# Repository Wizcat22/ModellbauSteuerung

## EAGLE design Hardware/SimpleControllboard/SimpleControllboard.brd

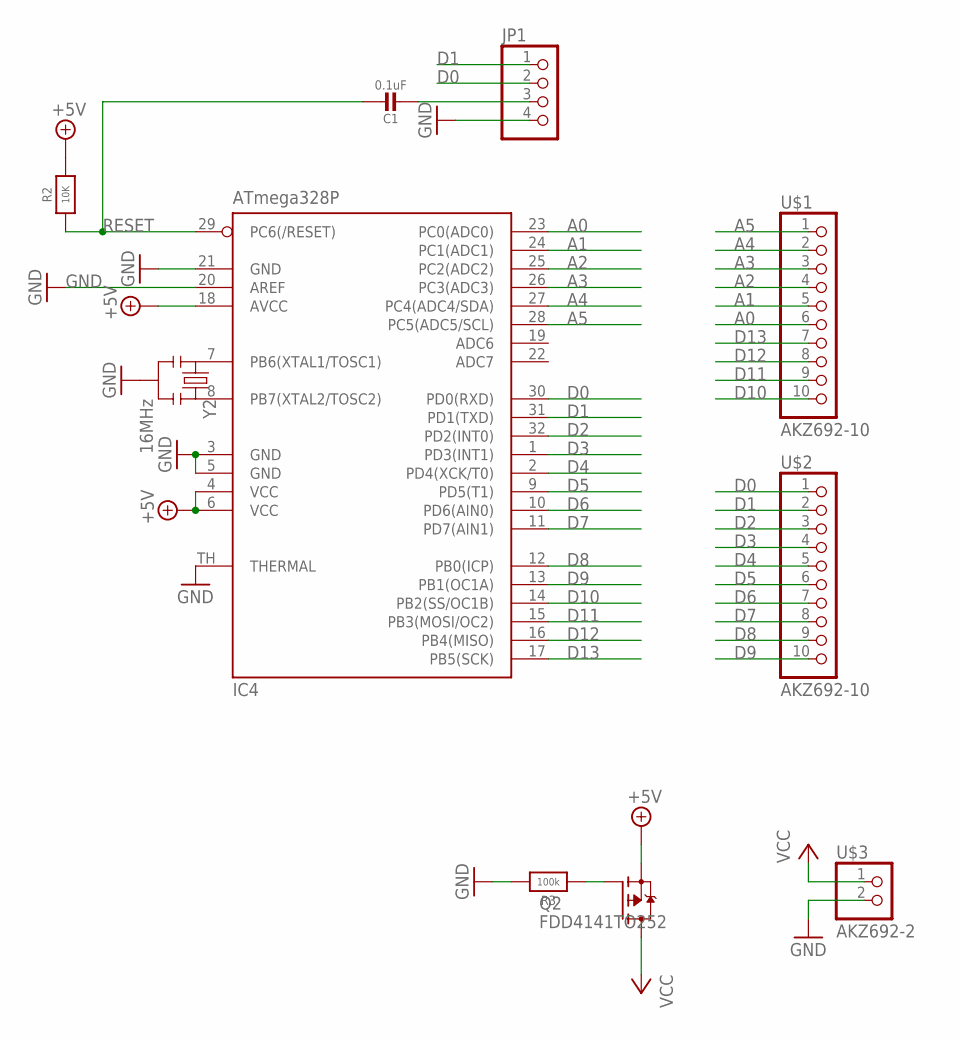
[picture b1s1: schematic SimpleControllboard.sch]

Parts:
C1: 0.1uF; 0805-NO
IC4: ATmega328P; MLF32-TH
JP1: PINHD-1X4; 1X04
Q2: FDD4141TO252; TO252
R2: 10K; 0805-NO
R3: 100k; 0805-NO
U$1, U$2: AKZ692-10; 1X10
U$3: AKZ692-2; 1X2
Y2: 16MHz; RESONATOR-SMD

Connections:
+5V: IC4.4 (VCC), IC4.6 (VCC), IC4.18 (AVCC), Q2.2 (S), R2.2
A0: IC4.23 (PC0(ADC0)), U$1.6
A1: IC4.24 (PC1(ADC1)), U$1.5
A2: IC4.25 (PC2(ADC2)), U$1.4
A3: IC4.26 (PC3(ADC3)), U$1.3
A4: IC4.27 (PC4(ADC4/SDA)), U$1.2
A5: IC4.28 (PC5(ADC5/SCL)), U$1.1
D0: IC4.30 (PD0(RXD)), JP1.2, U$2.1
D1: IC4.31 (PD1(TXD)), JP1.1, U$2.2
D2: IC4.32 (PD2(INT0)), U$2.3
D3: IC4.1 (PD3(INT1)), U$2.4
D4: IC4.2 (PD4(XCK/T0)), U$2.5
D5: IC4.9 (PD5(T1)), U$2.6
D6: IC4.10 (PD6(AIN0)), U$2.7
D7: IC4.11 (PD7(AIN1)), U$2.8
D8: IC4.12 (PB0(ICP)), U$2.9
D9: IC4.13 (PB1(OC1A)), U$2.10
D10: IC4.14 (PB2(SS/OC1B)), U$1.10
D11: IC4.15 (PB3(MOSI/OC2)), U$1.9
D12: IC4.16 (PB4(MISO)), U$1.8
D13: IC4.17 (PB5(SCK)), U$1.7
DTR/RTS1: C1.2, JP1.3
GND: IC4.3 (GND), IC4.5 (GND), IC4.20 (AREF), IC4.21 (GND), IC4.TH (THERMAL), JP1.4, R3.2, U$3.2, Y2.2
unnamed: IC4.8 (PB7(XTAL2/TOSC2)), Y2.3
unnamed: IC4.7 (PB6(XTAL1/TOSC1)), Y2.1
unnamed: Q2.1 (G), R3.1
RESET: C1.1, IC4.29 (PC6(/RESET)), R2.1
VCC: Q2.3 (D), U$3.1

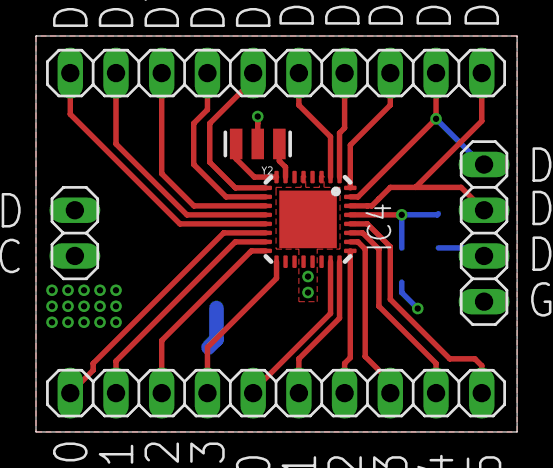
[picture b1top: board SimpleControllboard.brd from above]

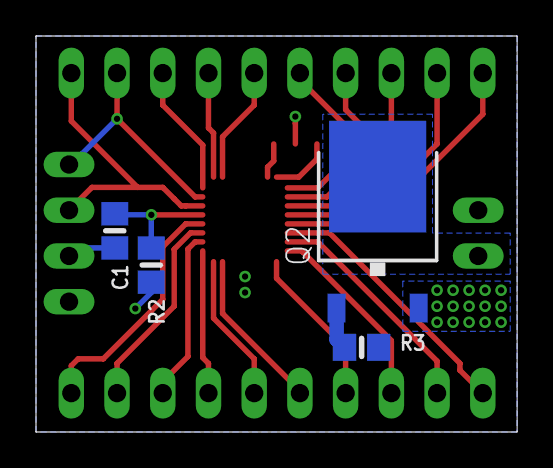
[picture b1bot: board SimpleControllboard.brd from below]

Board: 2 copper layers, 26.7 x 22.0 mm, 10 parts (4 on the bottom side), 28 nets.

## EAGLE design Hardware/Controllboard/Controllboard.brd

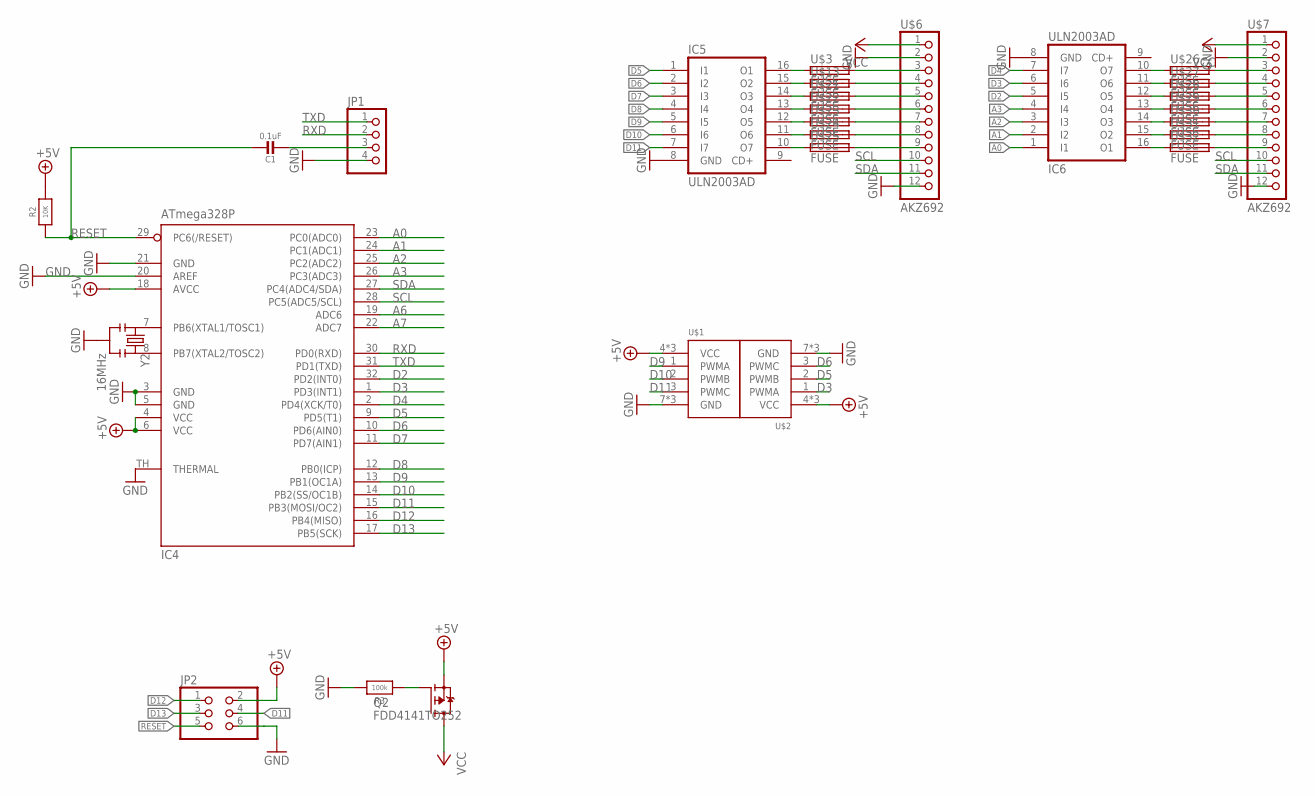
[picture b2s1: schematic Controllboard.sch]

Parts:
C1: 0.1uF; 0805-NO
IC4: ATmega328P; MLF32-TH
IC5, IC6: ULN2003AD; SO16
JP1: PINHD-1X4; 1X04
JP2: PINHD-2X3M; 2X03M
Q2: FDD4141TO252; TO252
R2: 10K; 0805-NO
R3: 100k; 0805-NO
U$1, U$2: SERVO_X3; 2X03/90
U$3, U$13, U$21, U$22, U$23, U$24, U$25, U$26, U$27, U$28, U$29, U$30, U$31, U$32: FUSE; C1206
U$6, U$7: AKZ692; 1X12
Y2: 16MHz; RESONATOR-SMD

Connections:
+5V: IC4.4 (VCC), IC4.6 (VCC), IC4.18 (AVCC), JP2.2, Q2.2 (S), R2.2, U$1.4 (VCC), U$1.5 (VCC), U$1.6 (VCC), U$2.4 (VCC), U$2.5 (VCC), U$2.6 (VCC)
A0: IC4.23 (PC0(ADC0)), IC6.1 (I1)
A1: IC4.24 (PC1(ADC1)), IC6.2 (I2)
A2: IC4.25 (PC2(ADC2)), IC6.3 (I3)
A3: IC4.26 (PC3(ADC3)), IC6.4 (I4)
A6: IC4.19 (ADC6)
A7: IC4.22 (ADC7)
D2: IC4.32 (PD2(INT0)), IC6.5 (I5)
D3: IC4.1 (PD3(INT1)), IC6.6 (I6), U$2.1 (PWMA)
D4: IC4.2 (PD4(XCK/T0)), IC6.7 (I7)
D5: IC4.9 (PD5(T1)), IC5.1 (I1), U$2.2 (PWMB)
D6: IC4.10 (PD6(AIN0)), IC5.2 (I2), U$2.3 (PWMC)
D7: IC4.11 (PD7(AIN1)), IC5.3 (I3)
D8: IC4.12 (PB0(ICP)), IC5.4 (I4)
D9: IC4.13 (PB1(OC1A)), IC5.5 (I5), U$1.1 (PWMA)
D10: IC4.14 (PB2(SS/OC1B)), IC5.6 (I6), U$1.2 (PWMB)
D11: IC4.15 (PB3(MOSI/OC2)), IC5.7 (I7), JP2.4, U$1.3 (PWMC)
D12: IC4.16 (PB4(MISO)), JP2.1
D13: IC4.17 (PB5(SCK)), JP2.3
DTR/RTS1: C1.2, JP1.3
GND: IC4.3 (GND), IC4.5 (GND), IC4.20 (AREF), IC4.21 (GND), IC4.TH (THERMAL), IC5.8 (GND), IC6.8 (GND), JP1.4, JP2.6, R3.2, U$1.7 (GND), U$1.8 (GND), U$1.9 (GND), U$2.7 (GND), U$2.8 (GND), U$2.9 (GND), U$6.2, U$6.12, U$7.2, U$7.12, Y2.2
unnamed: IC4.8 (PB7(XTAL2/TOSC2)), Y2.3
unnamed: IC4.7 (PB6(XTAL1/TOSC1)), Y2.1
unnamed: U$3.2, U$6.3
unnamed: U$6.4, U$13.2
unnamed: U$6.5, U$21.2
unnamed: U$6.6, U$22.2
unnamed: U$6.7, U$23.2
unnamed: U$6.8, U$24.2
unnamed: U$6.9, U$25.2
unnamed: U$7.3, U$26.2
unnamed: U$7.4, U$27.2
unnamed: U$7.5, U$28.2
unnamed: U$7.6, U$29.2
unnamed: U$7.7, U$30.2
unnamed: U$7.8, U$31.2
unnamed: U$7.9, U$32.2
unnamed: IC5.16 (O1), U$3.1
unnamed: IC5.15 (O2), U$13.1
unnamed: IC5.14 (O3), U$21.1
unnamed: IC5.13 (O4), U$22.1
unnamed: IC5.12 (O5), U$23.1
unnamed: IC5.11 (O6), U$24.1
unnamed: IC5.10 (O7), U$25.1
unnamed: IC6.10 (O7), U$26.1
unnamed: IC6.11 (O6), U$27.1
unnamed: IC6.12 (O5), U$28.1
unnamed: IC6.13 (O4), U$29.1
unnamed: IC6.14 (O3), U$30.1
unnamed: IC6.15 (O2), U$31.1
unnamed: IC6.16 (O1), U$32.1
unnamed: Q2.1 (G), R3.1
RESET: C1.1, IC4.29 (PC6(/RESET)), JP2.5, R2.1
RXD: IC4.30 (PD0(RXD)), JP1.2
SCL: IC4.28 (PC5(ADC5/SCL)), U$6.10, U$7.10
SDA: IC4.27 (PC4(ADC4/SDA)), U$6.11, U$7.11
TXD: IC4.31 (PD1(TXD)), JP1.1
VCC: Q2.3 (D), U$6.1, U$7.1

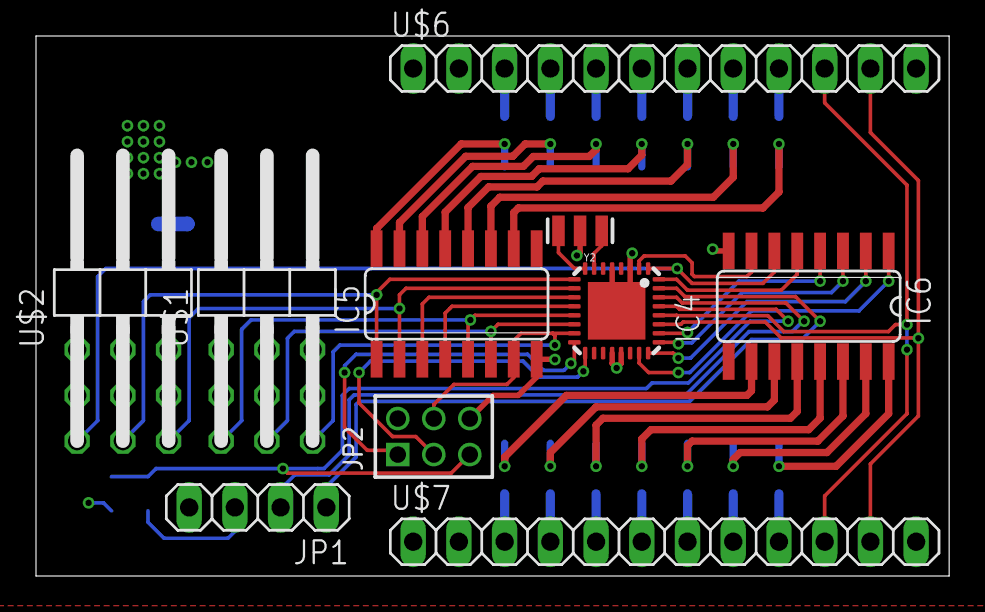
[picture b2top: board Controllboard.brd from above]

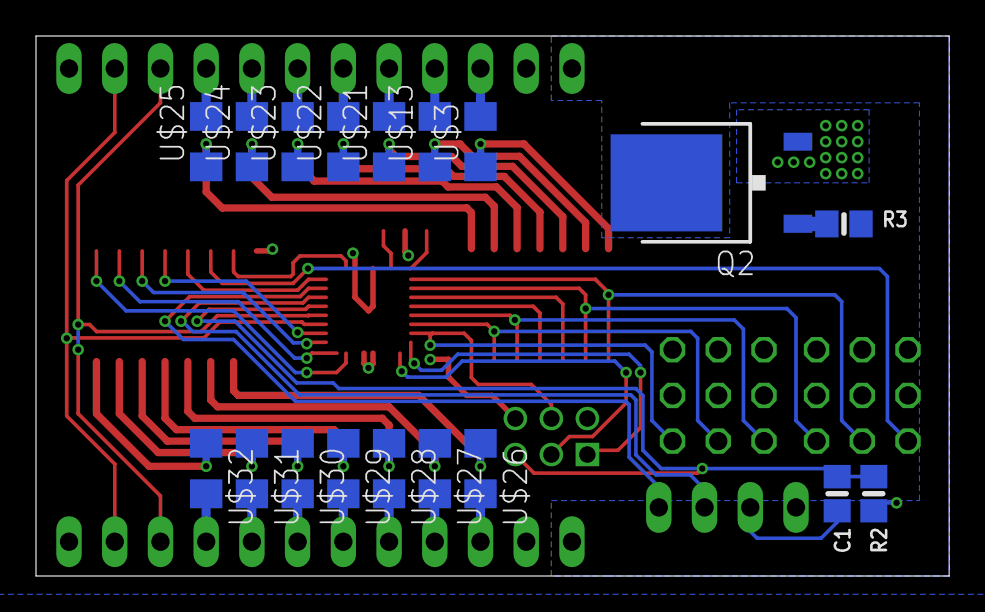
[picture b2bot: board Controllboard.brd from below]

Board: 2 copper layers, 50.7 x 30.0 mm, 28 parts (18 on the bottom side), 56 nets.

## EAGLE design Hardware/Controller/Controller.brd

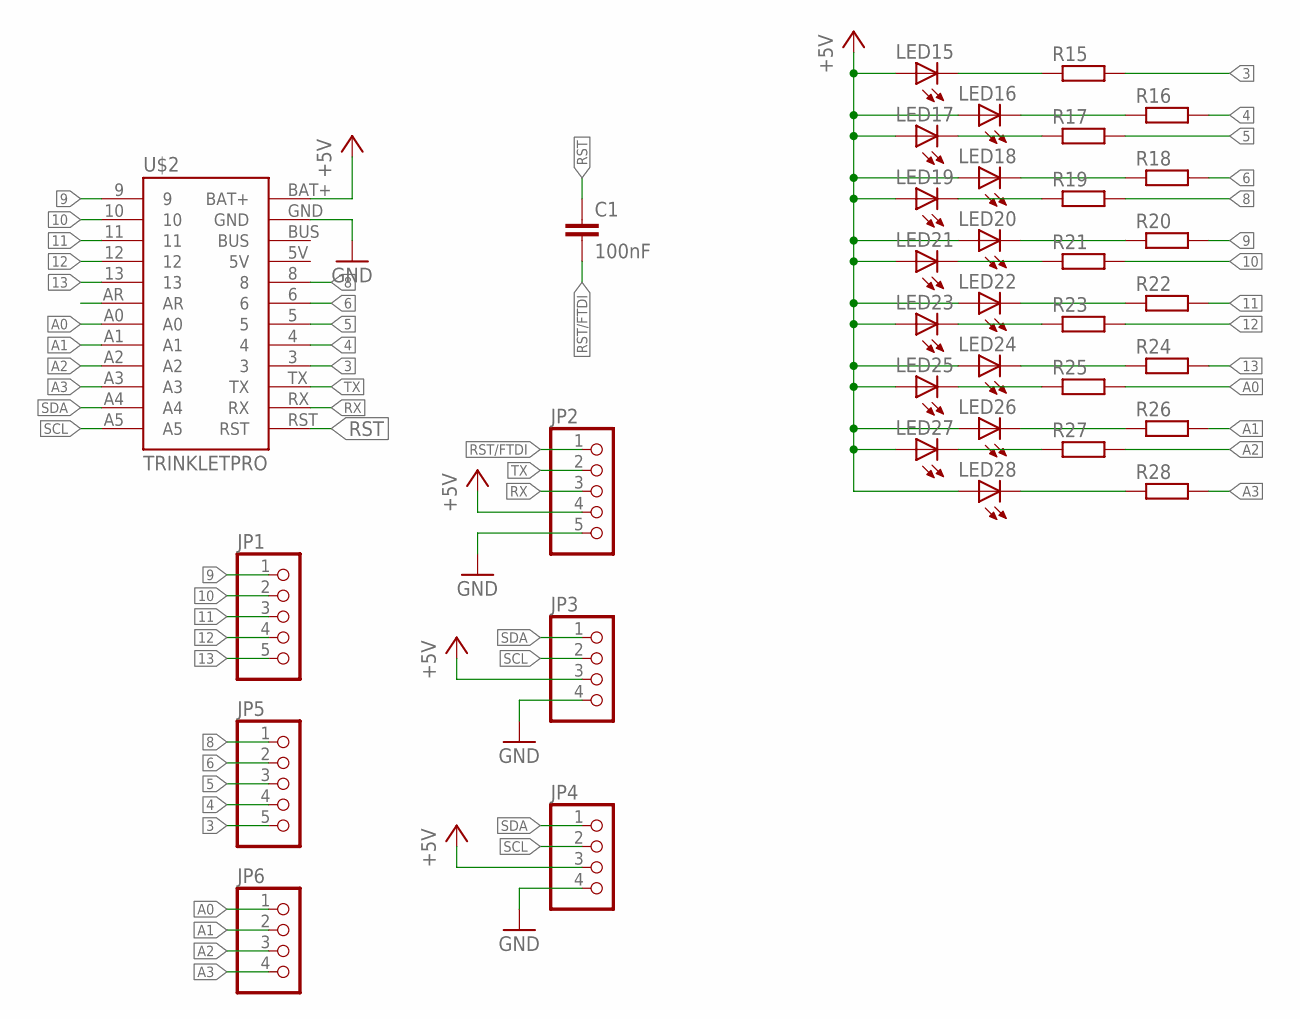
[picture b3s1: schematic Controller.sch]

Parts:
C1: 100nF; C0805
JP1, JP2, JP5: PINHD-1X5; 1X05
JP3, JP4, JP6: PINHD-1X4; 1X04
LED15, LED16, LED17, LED18, LED19, LED20, LED21, LED22, LED23, LED24, LED25, LED26, LED27, LED28: LEDCHIP-LED0805; CHIP-LED0805
R15, R16, R17, R18, R19, R20, R21, R22, R23, R24, R25, R26, R27, R28: R-EU_R0805; R0805
U$2: TRINKLETPRO; 1X12

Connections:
3: JP5.5, R15.2, U$2.3
4: JP5.4, R16.2, U$2.4
5: JP5.3, R17.2, U$2.5
6: JP5.2, R18.2, U$2.6
8: JP5.1, R19.2, U$2.8
9: JP1.1, R20.2, U$2.9
10: JP1.2, R21.2, U$2.10
11: JP1.3, R22.2, U$2.11
12: JP1.4, R23.2, U$2.12
13: JP1.5, R24.2, U$2.13
+5V: JP2.4, JP3.3, JP4.3, LED15.A, LED16.A, LED17.A, LED18.A, LED19.A, LED20.A, LED21.A, LED22.A, LED23.A, LED24.A, LED25.A, LED26.A, LED27.A, LED28.A, U$2.BAT+
A0: JP6.1, R25.2, U$2.A0
A1: JP6.2, R26.2, U$2.A1
A2: JP6.3, R27.2, U$2.A2
A3: JP6.4, R28.2, U$2.A3
GND: JP2.5, JP3.4, JP4.4, U$2.GND
unnamed: LED15.C, R15.1
unnamed: LED16.C, R16.1
unnamed: LED17.C, R17.1
unnamed: LED18.C, R18.1
unnamed: LED19.C, R19.1
unnamed: LED20.C, R20.1
unnamed: LED21.C, R21.1
unnamed: LED22.C, R22.1
unnamed: LED23.C, R23.1
unnamed: LED24.C, R24.1
unnamed: LED25.C, R25.1
unnamed: LED26.C, R26.1
unnamed: LED27.C, R27.1
unnamed: LED28.C, R28.1
RST: C1.1, U$2.RST
RST/FTDI: C1.2, JP2.1
RX: JP2.3, U$2.RX
SCL: JP3.2, JP4.2, U$2.A5
SDA: JP3.1, JP4.1, U$2.A4
TX: JP2.2, U$2.TX

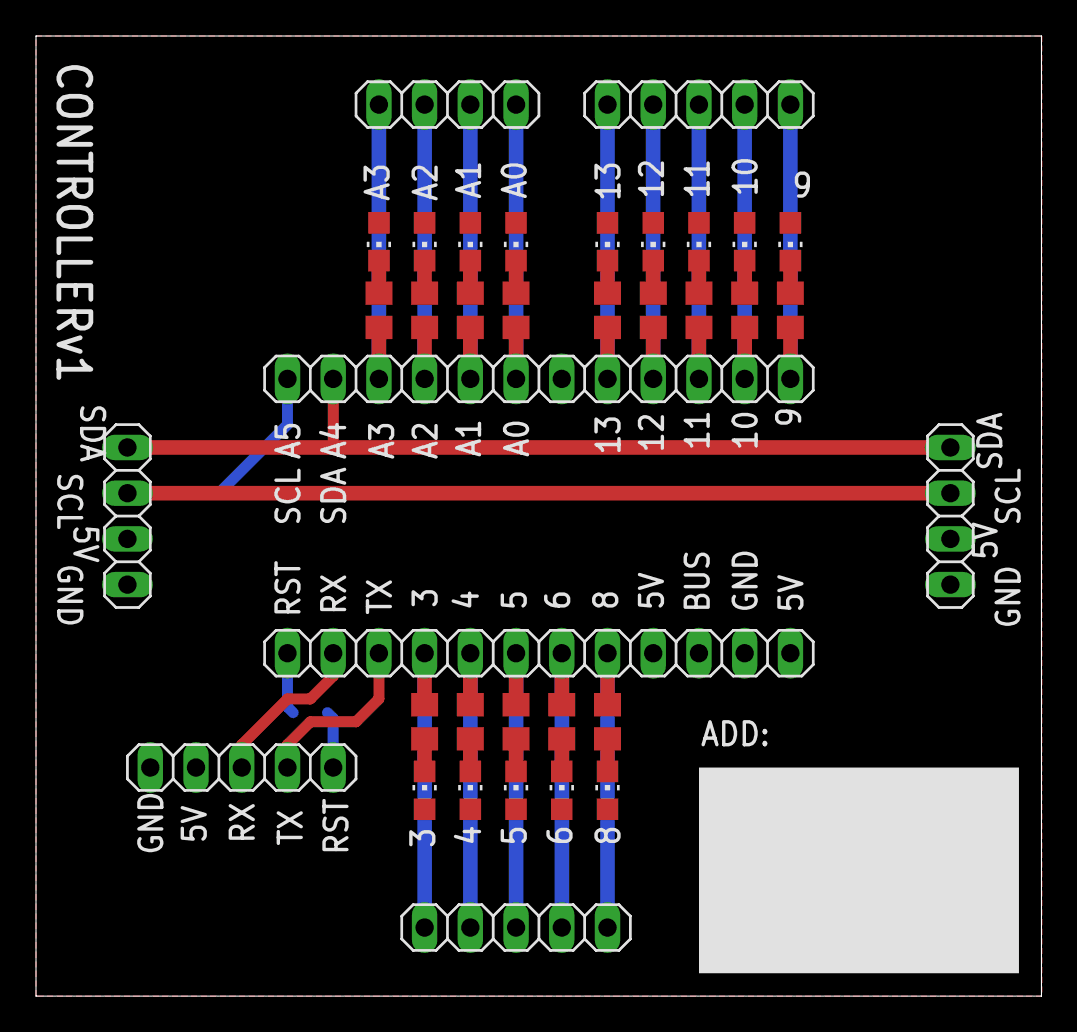
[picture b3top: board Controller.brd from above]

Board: 2 copper layers, 55.9 x 53.3 mm, 36 parts (1 on the bottom side), 36 nets.

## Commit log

2018-07-27 Initial Upload of PWM_Reader
2018-07-27 Initial Upload of Modellbausteuerung
2018-07-27 Initial Upload of Documents
2018-07-27 Initial Upload PCB
2018-10-24 New PCBs
2018-11-14 Update for new pcb
2019-01-24 Minor Improvements
2019-01-24 Deleted unused files
2019-03-19 Bugfixes, Added "Warnblinker"

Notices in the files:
parts and their libraries:
microbuilder: This work is placed in the public domain, and may be freely used for commercial and non-commercial work with the following conditions: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
SparkFun: Licensing: CC v3.0 Share-Alike You are welcome to use this library for commercial purposes.
